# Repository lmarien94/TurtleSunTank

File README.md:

# TurtleSunTank
Since reptiles are classified as ectothermic, which means that they are unable to regulate their body temperature internally and rely on the outer temperature. My turtles need a place to sun and with them growing their current sunningplace becomes a bit to small. Therefore I've designed an automated sun tank that can be placed on their current living space. Afcourse being an electronic enthousiast, the tank is fully automated.

It can perform the following tasks:
- Switch the lights automatically on/off based on the time,
- Adjust the lighting depending on the temperature & humidity in the sun tank,
- Switch the heating element for the water on/off based on the water temperature,
- Displaying the temperature & humidity in the sun tank on an LCD,
- Displaying the temperature of the water on an LCD.

For this project I've decided to design an small microcontroller based on an Atmega 2560 with an RTC on board:

Major components used in this project:
- MCU: Atmega 2560
- RTC: DS1307
- temperature sensor: DS18B20 (waterproof version)
- temperature & humidity sensor: DHT11
- LCD: standard 16x2 I2C LCD
- Relay module: standard 2 channel relay module

The project contains the following folders:
- PCB design: here you can find everything of the PCB design.
- 3D printing & lasercutting: an OpenSCAD model of the enclossure I've build (based on the The Ultimate Parametric Box by Heartman) and the design of the plexiglass used for the turtle sun tank.
- Code: the code written for the project.

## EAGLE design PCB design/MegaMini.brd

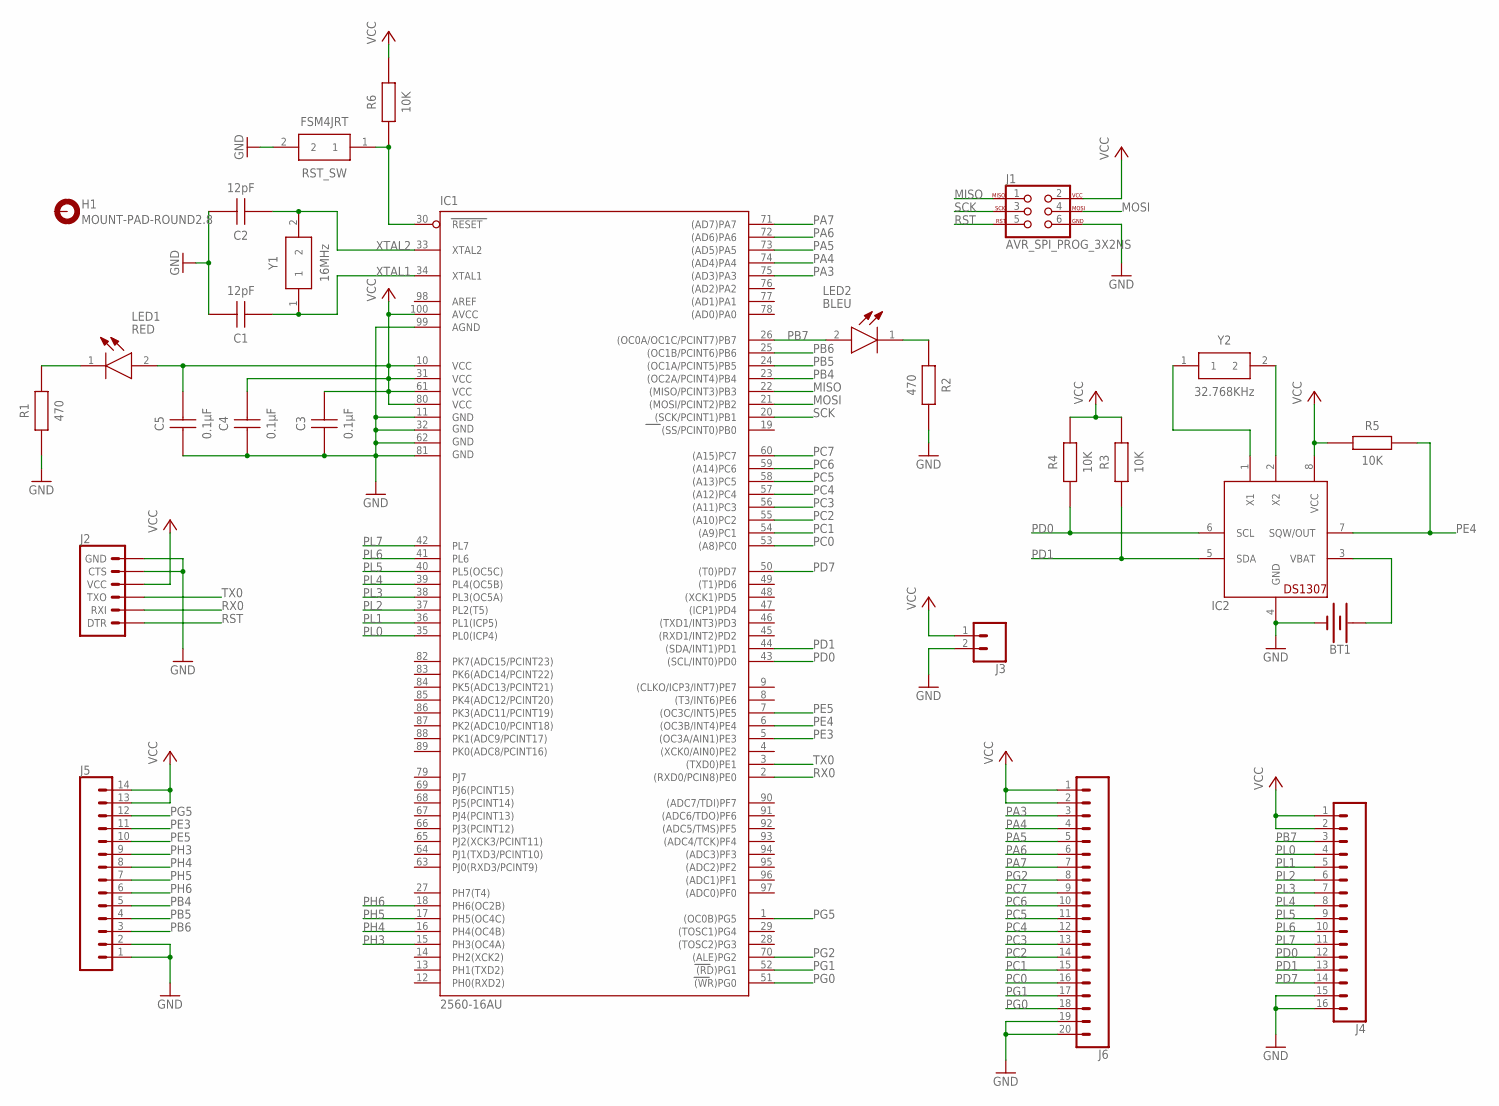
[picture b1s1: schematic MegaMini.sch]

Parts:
BT1: BATTERY-12MM_PTH; BATTCON_12MM_PTH
C1, C2: 12pF; CAPC3216X88N
C3, C4, C5: 0.1µF; CAPC3216X88N
H1: MOUNT-PAD-ROUND2.8; 2,8-PAD
IC1: 2560-16AU; TQFP100
IC2: DS1307; DIL08
J1: AVR_SPI_PROG_3X2NS; 2X3-NS
J2: 6_PIN_SERIAL_TARGET; 1X06
J3: CONN_02; 1X02
J4: CONN_16; 1X16
J5: CONN_14; 1X14
J6: CONN_20; 1X20
LED1: RED; LEDC1608X80N
LED2: BLEU; LEDC3214X78N
R1, R2: 470; RESC3116X70N
R3, R4, R5, R6: 10K; RESC3116X70N
RST_SW: FSM4JRT
Y1: 16MHz; FOXSDLF/120-20
Y2: 32.768KHz; FC-135

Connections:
GND: BT1.GND (-), C1.2, C2.2, C3.1, C4.1, C5.1, IC1.11 (GND), IC1.32 (GND1), IC1.62 (GND2), IC1.81 (GND3), IC1.99 (AGND), IC2.4 (GND), J1.6, J2.5 (CTS), J2.6 (GND), J3.2, J4.15, J4.16, J5.1, J5.2, J6.19, J6.20, R1.1, R2.2, RST_SW.2
MISO: IC1.22 ((MISO/PCINT3)PB3), J1.1
MOSI: IC1.21 ((MOSI/PCINT2)PB2), J1.4
unnamed: IC1.30 (RESET), R6.1, RST_SW.1
unnamed: IC2.1 (X1), Y2.1
unnamed: IC2.2 (X2), Y2.2
unnamed: LED1.1 (K), R1.2
unnamed: LED2.1 (K), R2.1
unnamed: BT1.VCC@1 (+), IC2.3 (VBAT)
PA3: IC1.75 ((AD3)PA3), J6.3
PA4: IC1.74 ((AD4)PA4), J6.4
PA5: IC1.73 ((AD5)PA5), J6.5
PA6: IC1.72 ((AD6)PA6), J6.6
PA7: IC1.71 ((AD7)PA7), J6.7
PB4: IC1.23 ((OC2A/PCINT4)PB4), J5.5
PB5: IC1.24 ((OC1A/PCINT5)PB5), J5.4
PB6: IC1.25 ((OC1B/PCINT6)PB6), J5.3
PB7: IC1.26 ((OC0A/OC1C/PCINT7)PB7), J4.3, LED2.2 (A)
PC0: IC1.53 ((A8)PC0), J6.16
PC1: IC1.54 ((A9)PC1), J6.15
PC2: IC1.55 ((A10)PC2), J6.14
PC3: IC1.56 ((A11)PC3), J6.13
PC4: IC1.57 ((A12)PC4), J6.12
PC5: IC1.58 ((A13)PC5), J6.11
PC6: IC1.59 ((A14)PC6), J6.10
PC7: IC1.60 ((A15)PC7), J6.9
PD0: IC1.43 ((SCL/INT0)PD0), IC2.6 (SCL), J4.12, R4.1
PD1: IC1.44 ((SDA/INT1)PD1), IC2.5 (SDA), J4.13, R3.1
PD7: IC1.50 ((T0)PD7), J4.14
PE3: IC1.5 ((OC3A/AIN1)PE3), J5.11
PE4: IC1.6 ((OC3B/INT4)PE4), IC2.7 (SQW/OUT), R5.2
PE5: IC1.7 ((OC3C/INT5)PE5), J5.10
PG0: IC1.51 ((WR)PG0), J6.18
PG1: IC1.52 ((RD)PG1), J6.17
PG2: IC1.70 ((ALE)PG2), J6.8
PG5: IC1.1 ((OC0B)PG5), J5.12
PH3: IC1.15 (PH3(OC4A)), J5.9
PH4: IC1.16 (PH4(OC4B)), J5.8
PH5: IC1.17 (PH5(OC4C)), J5.7
PH6: IC1.18 (PH6(OC2B)), J5.6
PL0: IC1.35 (PL0(ICP4)), J4.4
PL1: IC1.36 (PL1(ICP5)), J4.5
PL2: IC1.37 (PL2(T5)), J4.6
PL3: IC1.38 (PL3(OC5A)), J4.7
PL4: IC1.39 (PL4(OC5B)), J4.8
PL5: IC1.40 (PL5(OC5C)), J4.9
PL6: IC1.41 (PL6), J4.10
PL7: IC1.42 (PL7), J4.11
RST: J1.5, J2.1 (DTR)
RX0: IC1.2 ((RXD0/PCIN8)PE0), J2.2 (RXI)
SCK: IC1.20 ((SCK/PCINT1)PB1), J1.3
TX0: IC1.3 ((TXD0)PE1), J2.3 (TXO)
VCC: C3.2, C4.2, C5.2, IC1.10 (VCC), IC1.31 (VCC1), IC1.61 (VCC2), IC1.80 (VCC3), IC1.100 (AVCC), IC2.8 (VCC), J1.2, J2.4 (VCC), J3.1, J4.1, J4.2, J5.13, J5.14, J6.1, J6.2, LED1.2 (A), R3.2, R4.2, R5.1, R6.2
XTAL1: C1.1, IC1.34 (XTAL1), Y1.1
XTAL2: C2.1, IC1.33 (XTAL2), Y1.2

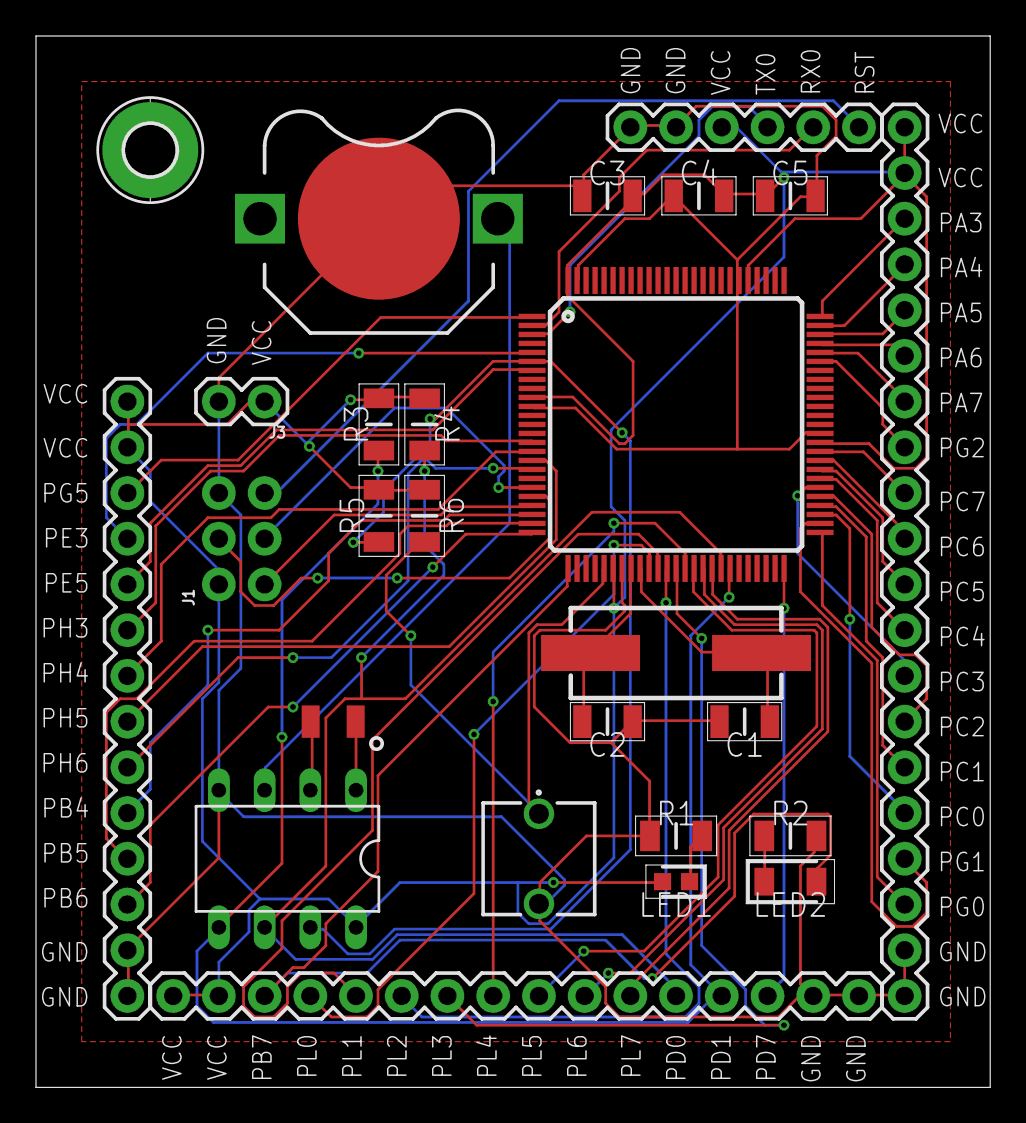
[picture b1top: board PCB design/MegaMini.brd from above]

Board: 2 copper layers, 53.0 x 58.4 mm, 27 parts (1 on the bottom side), 55 nets.

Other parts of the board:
U$1: OSHW-LOGO-L

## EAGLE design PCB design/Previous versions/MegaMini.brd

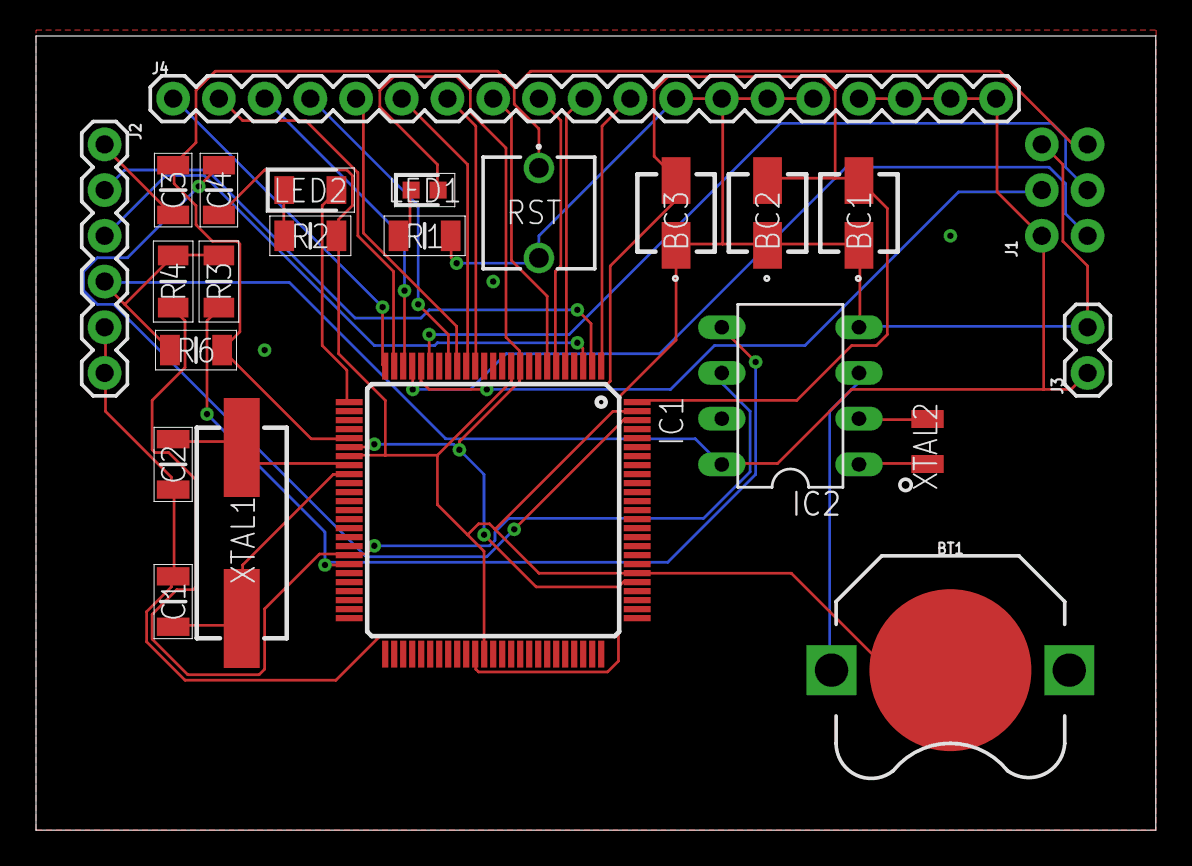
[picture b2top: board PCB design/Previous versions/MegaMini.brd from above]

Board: 2 copper layers, 62.2 x 44.1 mm, 24 parts (0 on the bottom side), 32 nets.

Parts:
BC1, BC2, BC3: 0.1µF; 865230640001
BT1: Keystone 3001; BATTCON_12MM_PTH
C1, C2: 12pF; CAPC3216X88N
C3, C4: 0.1µF; CAPC3216X90N
IC1: 2560-16AU; TQFP100
IC2: DS1307; DIL08
J1: AVR_SPI_PROG_3X2NS; 2X3-NS
J2: 1X06
J3: 1X02
J4: 1X19
LED1: RED; LEDC1608X80N
LED2: BLEU; LEDC3214X78N
R1, R2, R3, R4, R6: 10K; RESC3116X70N
RST: FSM4JRT
XTAL1: 16MHz, CL=10pF; FOXSDLF/120-20
XTAL2: 32.768KHz; FC-135

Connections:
5V: BC1.2, BC2.2, BC3.2, IC1.10, IC1.31, IC1.61, IC1.80, IC1.100, LED1.2
AREF: C4.2, IC1.98
DTR: C3.1, J2.1
GND: BC1.1, BC2.1, BC3.1, BT1.GND, C1.2, C2.1, C4.1, IC1.11, IC1.32, IC1.62, IC1.81, IC1.99, IC2.4, J1.6, J2.5, J2.6, J3.2, J4.12, J4.13, J4.14, J4.15, R1.1, R2.1, RST.2
MISO: IC1.22, J1.1
MOSI: IC1.21, J1.4
unnamed: LED1.1, R1.2
unnamed: LED2.1, R2.2
unnamed: IC2.1, XTAL2.1
unnamed: IC2.2, XTAL2.2
unnamed: BT1.VCC@1, IC2.3
PB4: IC1.23, J4.3
PB5: IC1.24, J4.2
PB6: IC1.25, J4.1
PB7: IC1.26, LED2.2
PD0: IC1.43, IC2.6, R4.1
PD1: IC1.44, IC2.5, R3.1
PE3: IC1.5, J4.10
PE4: IC1.6, J4.9
PE5: IC1.7, J4.8
PG5: IC1.1, J4.11
PH3: IC1.15, J4.7
PH4: IC1.16, J4.6
PH5: IC1.17, J4.5
PH6: IC1.18, J4.4
RST: C3.2, IC1.30, J1.5, R6.1, RST.1
RX0: IC1.2, J2.2
SCK: IC1.20, J1.3
TX0: IC1.3, J2.3
VCC: IC2.8, J1.2, J2.4, J3.1, J4.16, J4.17, J4.18, J4.19, R3.2, R4.2, R6.2
XTAL1: C1.1, IC1.34, XTAL1.1
XTAL2: C2.2, IC1.33, XTAL1.2

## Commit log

2017-11-12 Finished revision 1.0 of the schematic
2017-11-13 Finished the schematic
2017-11-14 revision 1.0 pcb design
2017-11-14 Finished revision 1.0 PCB and some major changes to the schematic
2017-11-14 small adjustements
2017-11-16 Some little improvements to the pcb
2017-11-17 Adjustements on the Atmel2560 package
2017-11-18 Added silkscreen, finished design.
    Everything is finished, generating gerber files for the board house.
2017-11-18 Generated gerber files
2017-11-23 Starting with the design of the 3D print
2017-11-28 Some small adjustements to the 3D print
2017-12-07 Added top for lasercutting
2017-12-10 Added some more lasercut files
2017-12-11 changed the screwholes in the top pannel
2017-12-31 Small adjustments
2017-12-31 Added some files and deleted others
2017-12-31 Added the enclosure for 3D printing
2017-12-31 Finished the portfolio and enclosure for 3D printing
2017-12-31 deleted temp .docx file
2018-01-07 Reorganized the repository
2018-01-07 Added a picture folder & some pictures
2018-01-08 Started on the code
2018-01-08 Added some changes to the code and folder with used libs
2018-01-08 Edited error with RST in PCB

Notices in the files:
parts and their libraries:
SparkFun-Batteries: Licensing: Creative Commons ShareAlike 4.0 International - https://creativecommons.org/licenses/by-sa/4.0
